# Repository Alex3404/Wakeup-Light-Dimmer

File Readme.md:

## Light Dimming on ESP32

A custom designed board using the ESP32 SoC, with an AC Dimming module. Before I get into the details I'd like to cover some of the backstory of this project. During my 2026 semester at my universtity, I had very early classes, and since it was till in the winter the sun doesn't come up by the time I need to wake up. I was reading some information online that waking up to a light is more natural way to wake up since it would memic the typical sun rise/sun set that humans evolved in. So I put that to the test, I had this smart light from Eufy and I programmed it to turn on 20-30minutes before I had to wake up. I saw that I woke up less grogy and more energietic in the mornings. However the biggest con with this approch was that there was no fade option. No way to graudually increase the light only pulse effects. So, I decided to fix this problem myself. I saw that I had an over head light in my room, and a light switch that could be dimmable. Why not combine a sunrise alarm clock with a light switch dimmer? So I got to work. This is project is the result of that question.

## Fully Async Rust Firmware

I landed on the ESP32 for a few main reasons: its direct support for writing in Rust supporting Embassy, its diverse set of peripherals, and that it has WiFI & Bluetooth Module. This repo has the Rust project in its root directory, I've split a few different operations into packages. A application library for unit testing my code, a binary that loads the appliction library on the ESP32, a supporting async storage-derive for the async app state storage driver using the ESP32 NVS partition, and a crate sequental storage built for writing in the format the ESP32 expects.

### Slint UI

My project uses the Slint UI framework for compiling the UI files into the native executable.

## Future Direction for this Project

Currently I'm still working on this project as a solo adventure. If you have issues with it or find any bugs open an issue! I'll get to it. Right now I am still working on the PCB design, Ive gone through 4 iterations now on the PCB, with the last two not working at all for trivial reasons. Once I didn't impedence match the USB data traces to 90 ohms, and another time I shorted the VCC and Ground layers ( Facepalm ). I'm working on PCB design that should work, and will incorperate all my plans.

* Real Time Clock
* SPI Interface for TFT Display
* ESP32
* MOSFET AC Dimming for LCD bulbs
* LiPo battery backup for RTC with intergrated battery charger

I'm also working on the firmware currently I am striving towards getting WIFI and bluethooth to work, then after that I'd love to focus on an Phone application inorder to configure alarm times, and other options exposed though either WIFI or Bluetooth. I'm leaning towards Bluetooth due to WiFi insecurities relating to IoT devices. Supporting only bluetooth should reduce the attack vector.

## Video Showcase

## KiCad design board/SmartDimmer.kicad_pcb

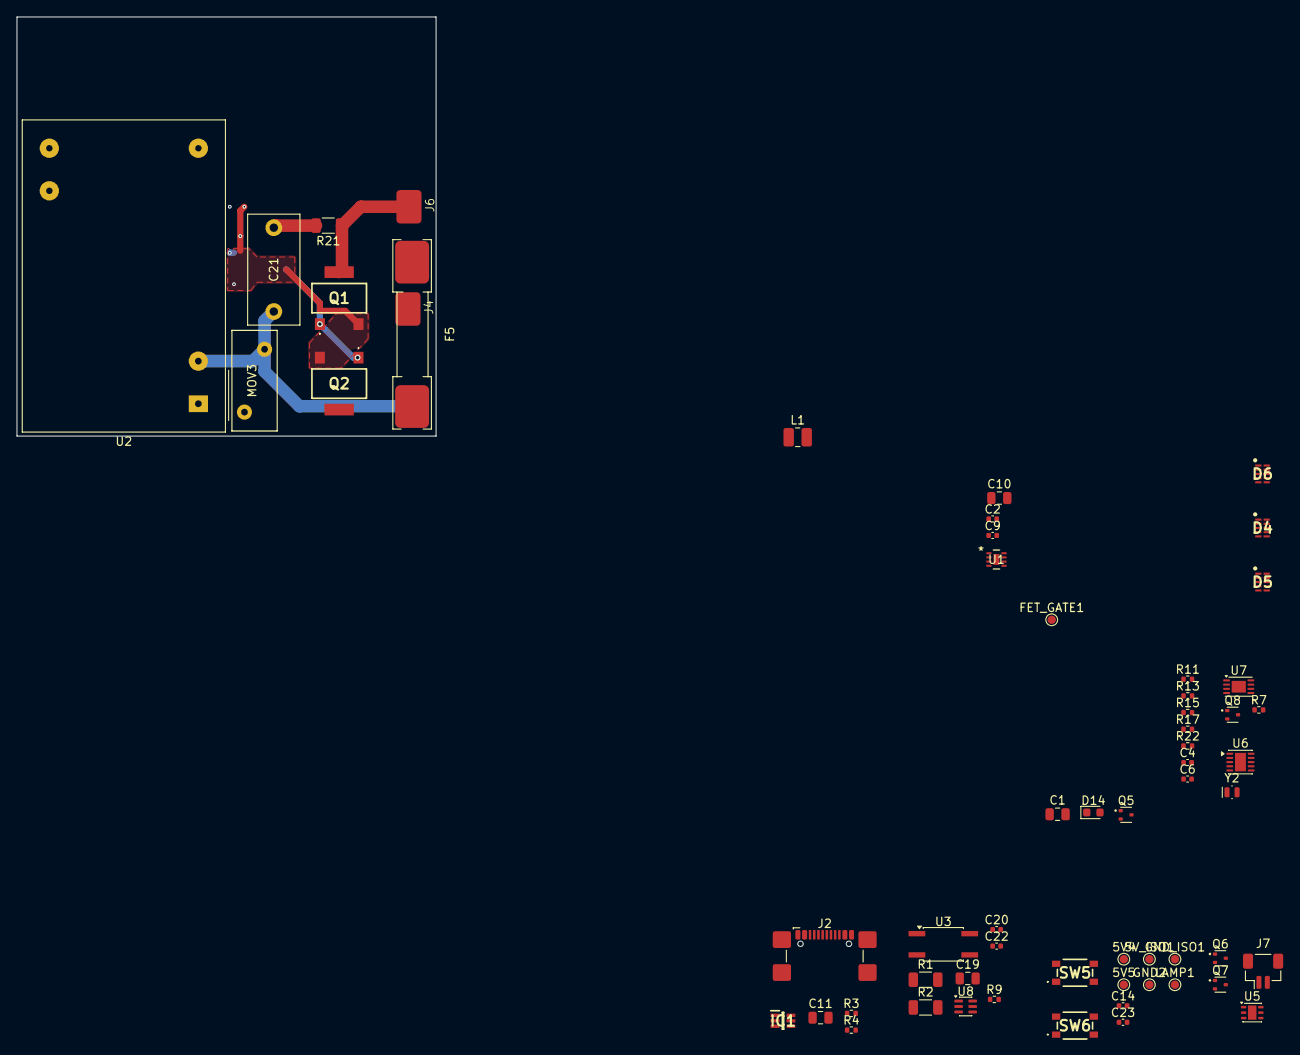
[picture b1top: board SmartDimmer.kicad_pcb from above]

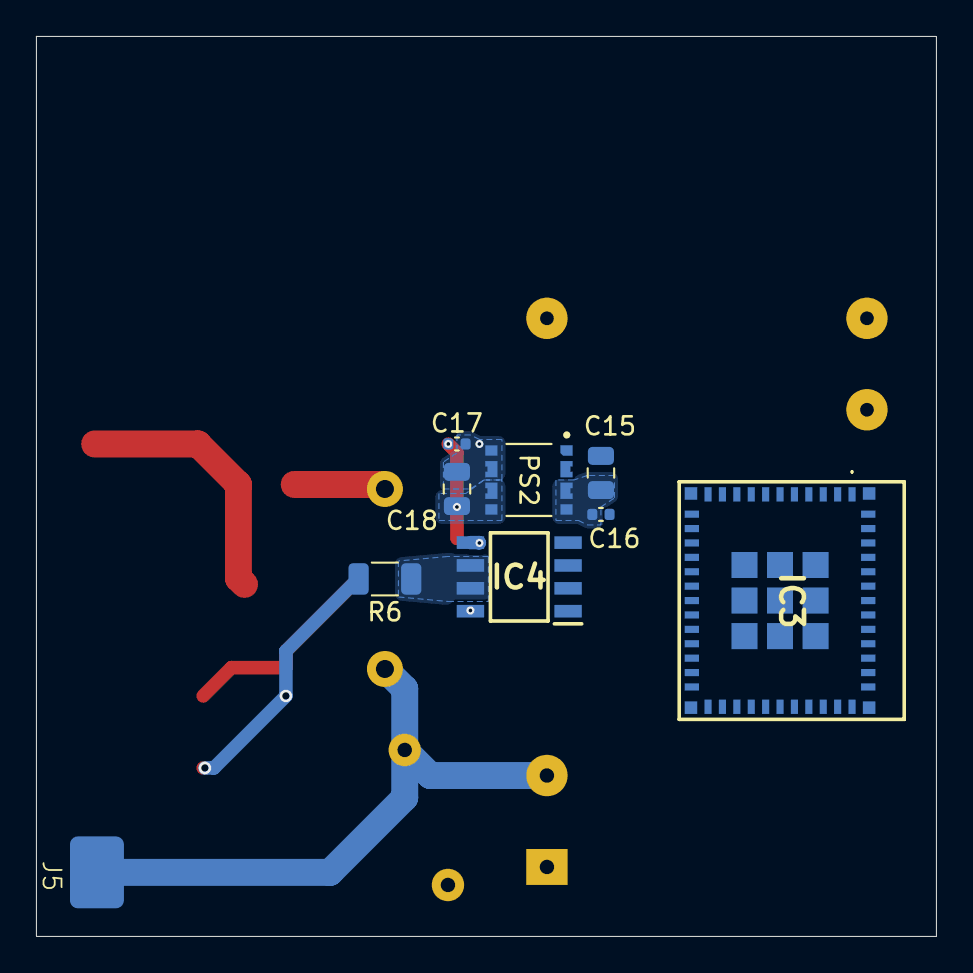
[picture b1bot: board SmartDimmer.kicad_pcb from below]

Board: 6 copper layers, 50.0 x 50.0 mm, 69 parts (9 on the bottom side), 50 nets.

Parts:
5V4, 5V5, 5V_ISO1: TestPoint; TestPoint_Pad_D1.0mm
C1, C11, C15, C18, C19: 10uF; C_0805_2012Metric
C2: 4.7uF; C_0402_1005Metric
C4, C6: 1uF; C_0402_1005Metric
C9: 520pF; C_0402_1005Metric
C10: 22uF; C_0805_2012Metric
C14, C16, C17, C20, C22, C23: 100nF; C_0402_1005Metric
C21: B32921C3104M000; C_Rect_L13.0mm_W6.0mm_P10.00mm_FKS3_FKP3_MKS4
D4, D5, D6: PUSB3AB4Z; SON50P100X250X50-10N
D14: MAIN_PWR_ST; D_0603_1608Metric
F5: Fuse; 3561KTR_SMD_FUSE_CLIP
FET_GATE1: TestPoint; TestPoint_Pad_D1.0mm
GND2: TestPoint; TestPoint_Pad_D1.0mm
GND_ISO1: TestPoint; TestPoint_Pad_D1.0mm
IC1: NUF2221W1T2G; SOT65P210X110-6N
IC3: ESP32-C6-MINI-1U-H4; ESP32C6MINI1UH4
IC4: 1EDB7275F; SOIC127P600X175-8N
J2: USB-C-16Pin; USB_C_Receptacle_GCT_USB4110
J4, J5, J6: Conn_01x01; Solder_Conn_01x01
J7: BATTERY; JST_SH_BM02B-SRSS-TB_1x02-1MP_P1.00mm_Vertical
L1: 2.2uH; L_1008_2520Metric
LAMP1: TestPoint; TestPoint_Pad_D1.0mm
MOV3: B72210S2271K101; RV_Disc_D12mm_W5.4mm_P7.5mm
PS2: R05C1TF05S-R; CONV_R05C1TF05S-R
Q1, Q2: IPN70R600P7SATMA1
Q5, Q6, Q7, Q8: SSF2320Y; SOT-523
R1, R2: 2/3W 47kΩ; R_1206_3216Metric
R3, R4: 5.1k; R_0402_1005Metric
R6, R21: 100Ω 1W; R_1206_3216Metric
R7: 68K; R_0402_1005Metric
R9: 20k; R_0402_1005Metric
R11, R17, R22: 3.3k; R_0402_1005Metric
R13: 100; R_0402_1005Metric
R15: 10k; R_0402_1005Metric
SW5, SW6: TL3365AF180QG
U1: MIC23050-SYML-TR; MLF-8_ML_MCH-L
U2: IRM-03-5; Converter_ACDC_MeanWell_IRM-03-xx_THT
U3: LTV-354T-A; SO-4_4.4x3.6mm_P2.54mm
U5: NCV68261; DFN-6-1EP_2x2mm_P0.65mm_EP1.01x1.7mm
U6: PCF85063ATL; DFN-10-1EP_2.6x2.6mm_P0.5mm_EP1.3x2.2mm
U7: MCP73831-2-MC; DFN-8-1EP_3x2mm_P0.5mm_EP1.7x1.4mm
U8: NC7WZ14P6X; SOT-363_SC-70-6
Y2: Crystal_Small; Crystal_SMD_MicroCrystal_CM9V-T1A-2Pin_1.6x1.0mm

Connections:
+3.3V: 5V5.1 (1_1), C1.1, C4.1, C9.2, C10.1, C19.1, C20.1, C22.1, D14.2 (A), IC3.3 (3V3), IC4.1 (VDDI), L1.2, R9.2, R11.1, R15.1, R17.1, R22.1, U1.4 (SNS), U8.5 (V_{CC})
+5V: 5V4.1 (1_1), C2.1, C15.1, C16.1, PS2.4_5 (VIN+), PS2.6 (CTRL), U1.2 (EN), U1.7 (VIN), U2.16 (+Vo), U7.1 (V_{DD}), U7.2 (V_{DD})
+5V_ISO: 5V_ISO1.1 (1_1), C17.2, C18.2, IC4.5 (VDDO), PS2.10_11 (VOUT-), PS2.12 (VOUT-)
/AC_Protection1/LINE_IN: F5.1, J4.1 (Pin_1_1)
/A_IN: D5.5 (CH4), IC3.6 (IO3)
/BOOT: C23.1, D6.5 (CH4), IC3.23 (IO9), SW6.3 (K), SW6.4 (A)
/B_IN: D6.1 (CH1), IC3.9 (IO4)
/Battery Charger/+BATT: Q7.3 (D), Q8.1 (G), U5.3 (D), U5.4 (EN), U6.10 (VDD), U7.3 (V_{BAT}), U7.4 (V_{BAT})
/ENCODER_SW: D6.2 (CH2), IC3.10 (IO5)
/ESP32-MCU/LED: IC3.28 (IO22), Q5.1 (G)
/ESP32-MCU/STRAP_GPIO8: IC3.22 (IO8), R17.2
/ESP32-MCU/USB_D+: IC1.4 (D2(C)), IC3.18 (IO13)
/ESP32-MCU/USB_D-: IC1.6 (D1(C)), IC3.17 (IO12)
/Isolated MOSFET Dimmer/FET_GATE: FET_GATE1.1 (1_1), Q1.1 (G), Q2.1 (G), R6.2
/MISO: D4.4 (CH3), IC3.20 (IO15)
/MOSI: D4.2 (CH2), IC3.19 (IO14)
/Protected Battery Connector/+BATT_IN: J7.1, Q6.3 (D)
/RESERVED: D5.4 (CH3), IC3.16 (IO7)
/SCL: D5.2 (CH2), IC3.13 (IO1), R11.2, U6.7 (SCL)
/SCLK: D4.1 (CH1), IC3.24 (IO18)
/SDA: D5.1 (CH1), IC3.12 (IO0), R22.2, U6.6 (SDA)
/USB-C/VBUS: C11.1, IC1.5 (VBUS), J2.A4 (VBUS), J2.A9 (VBUS), J2.B4 (VBUS), J2.B9 (VBUS)
/~LED_CS: D4.5 (CH4), IC3.25 (IO19)
/~RESET: C6.1, C14.1, D6.4 (CH3), IC3.8 (EN), R15.2, SW5.3 (K), SW5.4 (A)
GND: C1.2, C2.2, C4.2, C6.2, C10.2, C11.2, C14.2, C15.2, C16.2, C19.2, C20.2, C22.2, C23.2, D4.3 (GND), D4.8 (GND), D5.3 (GND), D5.8 (GND), D6.3 (GND), D6.8 (GND), GND2.1 (1_1), IC1.2 (GND), IC3.1 (GND), IC3.2 (GND), IC3.11 (GND), IC3.14 (GND), IC3.36 (GND), IC3.37, IC3.38 (GND), IC3.39 (GND), IC3.40 (GND), IC3.41 (GND), IC3.42 (GND), IC3.43 (GND), IC3.44 (GND), IC3.45 (GND), IC3.46 (GND), IC3.47 (GND), IC3.48 (GND), IC3.49 (GND), IC3.50 (GND), IC3.51 (GND), IC3.52 (GND), IC3.53 (GND), IC3.54 (GND), IC3.55 (GND), IC3.56 (GND), IC3.57 (GND), IC3.58 (GND), IC3.59 (GND), IC3.60 (GND), IC3.61 (GND), IC4.3 (IN-), IC4.4 (GNDI), J2.A1 (GND), J2.A12 (GND), J2.B1 (GND), J2.B12 (GND), J2.SH (SHIELD), J7.2, J7.MP (MountPin), PS2.1 (VIN-), PS2.2_3 (VIN-), Q5.2 (S), Q8.2 (S), R3.1, R4.1, SW5.1, SW5.2, SW6.1, SW6.2, U1.6 (AGND), U1.8 (PGND), U1.9, U2.14 (-Vo), U3.3, U5.5 (GND), U6.5 (VSS), U7.6 (V_{SS}), U8.2 (GND)
GND_ISO: C17.1, C18.1, GND_ISO1.1 (1_1), IC4.8 (GNDO), PS2.7 (VSEL), PS2.8_9 (VOUT+), Q1.3 (S), Q2.3 (S)
LAMP_GATE: IC3.27 (IO21), IC4.2 (IN+), LAMP1.1 (1_1)
LINE: F5.2, MOV3.2, Q2.2 (D), R2.1, U2.1 (AC/L)
LOAD: J6.1 (Pin_1_1), Q1.2 (D), R21.1
NEUT: C21.2, J5.1 (Pin_1_1), MOV3.1, R1.1, U2.3 (AC/N)
unnamed: C21.1, R21.2
unnamed: D14.1 (K), R13.2
unnamed: IC1.1 (D1(I)), J2.A7 (D-), J2.B7 (D-)
unnamed: IC1.3 (D2(I)), J2.A6 (D+), J2.B6 (D+)
unnamed: IC4.6 (OUT_SRC), IC4.7 (OUT_SNK), R6.1
unnamed: J2.A5 (CC1), R4.2
unnamed: J2.B5 (CC2), R3.2
unnamed: Q5.3 (D), R13.1
unnamed: Q6.1 (G), Q7.1 (G), U5.2 (G)
unnamed: Q6.2 (S), Q7.2 (S), U5.1 (S), U5.6 (IN)
unnamed: Q8.3 (D), R7.2
unnamed: R1.2, U3.2
unnamed: R2.2, U3.1
unnamed: C9.1, U1.5 (CFF)
unnamed: L1.1, U1.1 (SW)
unnamed: U6.1 (OSCI), Y2.1
unnamed: U6.2 (OSCO), Y2.2
unnamed: R7.1, U7.8 (PROG)
unnamed: R9.1, U3.4, U8.1 (1A)
ZERO_CROSS: IC3.26 (IO20), U8.6 (1Y)

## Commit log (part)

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2026-03-21 Inital
2026-03-22 Revision
    Working lamp dimmer and pulse scheduler. Pulse scheduler uses RMT for microsecond precision. Light bulb still flashes occasionally meaning timing is wrong.
2026-03-23 Faster lamp dimmer without using pulse scheduler keeping it for later use?
2026-03-23 pre adding embassy support
2026-03-25 display
2026-03-31 Intergrating new MCPWM driver in my esp-hal-mcpwm-cap repo
    Using MCPWM should give me a light dimmer timing that is controlled by hardware, so during wifi/bluetooth operations there will be no flicker.
2026-04-02 Some updates
2026-04-05 Dimmer working with MCPWM
2026-04-09 Huge changes
2026-04-27 Refactored to remove most dynamically allocated referenses for referances that would be known at compile time
2026-04-27 Moved some files around
